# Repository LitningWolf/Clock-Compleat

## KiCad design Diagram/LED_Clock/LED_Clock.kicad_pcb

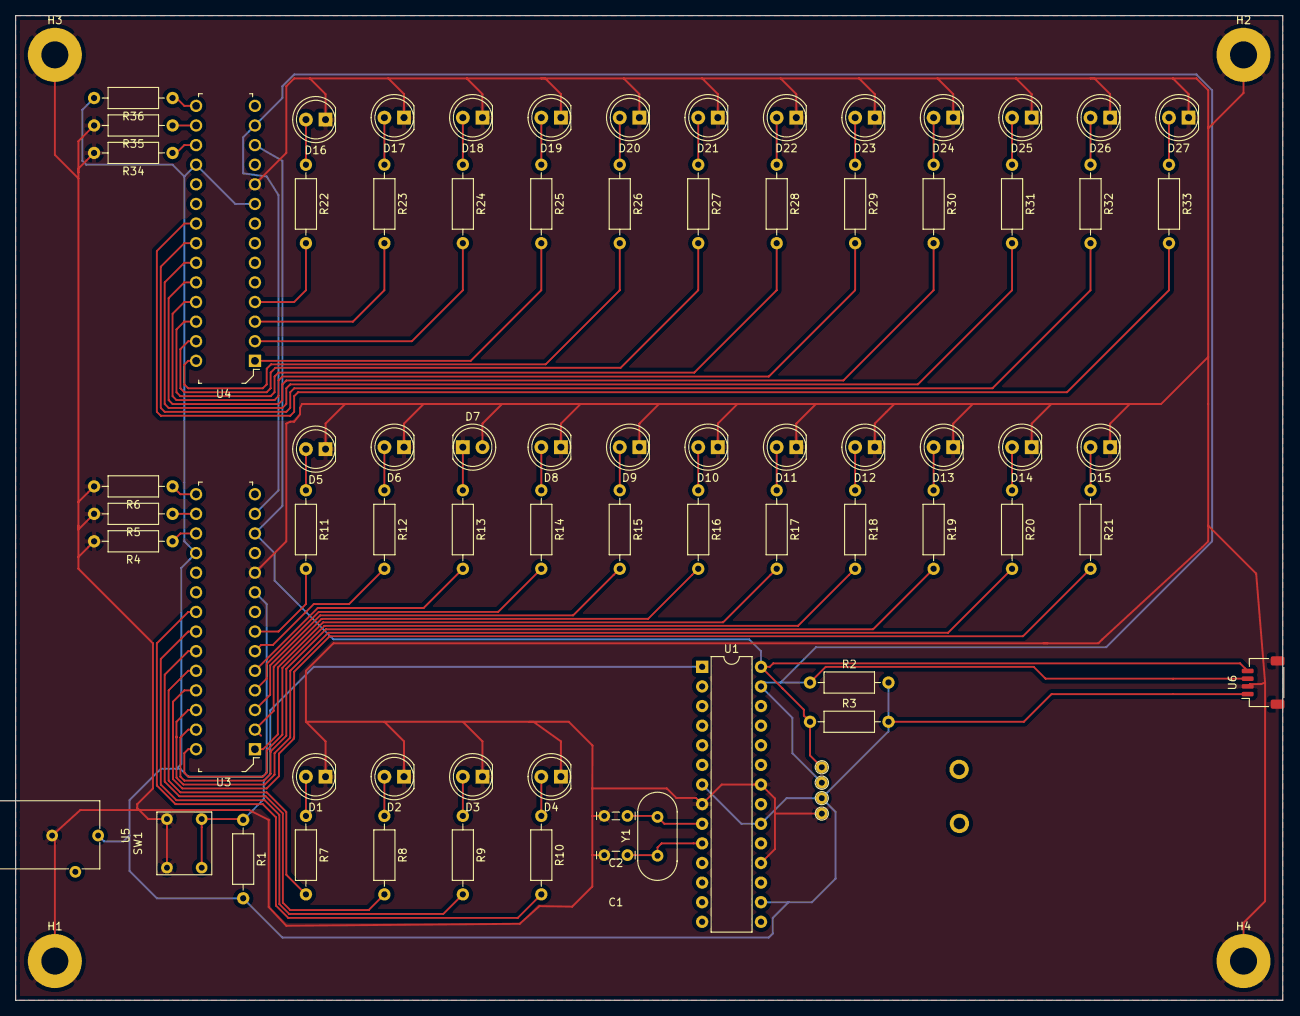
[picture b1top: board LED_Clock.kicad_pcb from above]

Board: 2 copper layers, 164.1 x 127.5 mm, 77 parts (0 on the bottom side), 67 nets.

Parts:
C1, C2: Capacitor
D1, D2, D3, D4, D5, D6, D7, D8, D9, D10, D11, D12, D13, D14, D15, D16, D17, D18, D19, D20, D21, D22, D23, D24, D25, D26, D27: Blue; LED_D5.0mm
H1, H2, H3, H4: MountingHole_Pad; MountingHole_3.5mm_Pad
R1, R4, R5, R6, R7, R8, R9, R10, R11, R12, R13, R14, R15, R16, R17, R18, R19, R20, R21, R22, R23, R24, R25, R26, R27, R28, R29, R30, R31, R32, R33, R34, R35, R36: 1k; R_Axial_DIN0207_L6.3mm_D2.5mm_P10.16mm_Horizontal
R2, R3: 4.7k; R_Axial_DIN0207_L6.3mm_D2.5mm_P10.16mm_Horizontal
SW1: SW_Push_Dual; Pushbutton
U1: ATmega328P-PU; DIP-28_W7.62mm
U2: DS3231MZ; DS3231
U3, U4: MCP23017-E_SP; DIP-28_W7.62mm
U5: Barreljack; BarrelJack
U6: JST4pin; JST_SH_SM04B-SRSS-TB_1x04-1MP_P1.00mm_Horizontal
Y1: Crystal

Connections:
+5V: R1.2, R2.2, R3.2, R36.2, U1.7, U1.20, U2.2, U3.9, U3.18, U4.9, U4.18, U5.1, U6.1
/clock minute/SCL: R3.1, U1.28, U2.8, U3.12, U4.12, U6.4
/clock minute/SDA: R2.1, U1.27, U2.7, U3.13, U4.13, U6.3
GND: C1.2, C2.2, D1.1, D2.1, D3.1, D4.1, D5.1, D6.1, D7.1, D8.1, D9.1, D10.1, D11.1, D12.1, D13.1, D14.1, D15.1, D16.1, D17.1, D18.1, D19.1, D20.1, D21.1, D22.1, D23.1, D24.1, D25.1, D26.1, D27.1, H1.1, H2.1, H3.1, H4.1, R4.2, R5.2, R6.2, R34.2, R35.2, SW1.2, SW1.4, U1.8, U1.22, U2.5, U3.10, U4.10, U5.2, U6.2, U6.MP
unnamed: C1.1, U1.10, Y1.1
unnamed: C2.1, U1.9, Y1.2
unnamed: D1.2, R7.1
unnamed: D2.2, R8.1
unnamed: D3.2, R9.1
unnamed: D4.2, R10.1
unnamed: D5.2, R11.1
unnamed: D6.2, R12.1
unnamed: D7.2, R13.1
unnamed: D8.2, R14.1
unnamed: D9.2, R15.1
unnamed: D10.2, R16.1
unnamed: D11.2, R17.1
unnamed: D12.2, R18.1
unnamed: D13.2, R19.1
unnamed: D14.2, R20.1
unnamed: D15.2, R21.1
unnamed: D16.2, R22.1
unnamed: D17.2, R23.1
unnamed: D18.2, R24.1
unnamed: D19.2, R25.1
unnamed: D20.2, R26.1
unnamed: D21.2, R27.1
unnamed: D22.2, R28.1
unnamed: D23.2, R29.1
unnamed: D24.2, R30.1
unnamed: D25.2, R31.1
unnamed: D26.2, R32.1
unnamed: D27.2, R33.1
unnamed: R1.1, SW1.1, SW1.3, U1.1
unnamed: R4.1, U3.17
unnamed: R5.1, U3.16
unnamed: R6.1, U3.15
unnamed: R7.2, U3.24
unnamed: R8.2, U3.23
unnamed: R9.2, U3.22
unnamed: R10.2, U3.21
unnamed: R11.2, U3.7
unnamed: R12.2, U3.6
unnamed: R13.2, U3.5
unnamed: R14.2, U3.4
unnamed: R15.2, U3.3
unnamed: R16.2, U3.2
unnamed: R17.2, U3.1
unnamed: R18.2, U3.28
unnamed: R19.2, U3.27
unnamed: R20.2, U3.26
unnamed: R21.2, U3.25
unnamed: R22.2, U4.4
unnamed: R23.2, U4.3
unnamed: R24.2, U4.2
unnamed: R25.2, U4.1
unnamed: R26.2, U4.28
unnamed: R27.2, U4.27
unnamed: R28.2, U4.26
unnamed: R29.2, U4.25
unnamed: R30.2, U4.24
unnamed: R31.2, U4.23
unnamed: R32.2, U4.22
unnamed: R33.2, U4.21
unnamed: R34.1, U4.17
unnamed: R35.1, U4.16
unnamed: R36.1, U4.15

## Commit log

2020-04-09 Ground Plane
    added a Ground plane and some missing traces.
2020-04-16 Updated
    led flipped the RTS symbol remade and JST4pin enlarged
2020-04-16 update 1.2
    new mounting holes jst4 pin mounting points to ground and refilled
